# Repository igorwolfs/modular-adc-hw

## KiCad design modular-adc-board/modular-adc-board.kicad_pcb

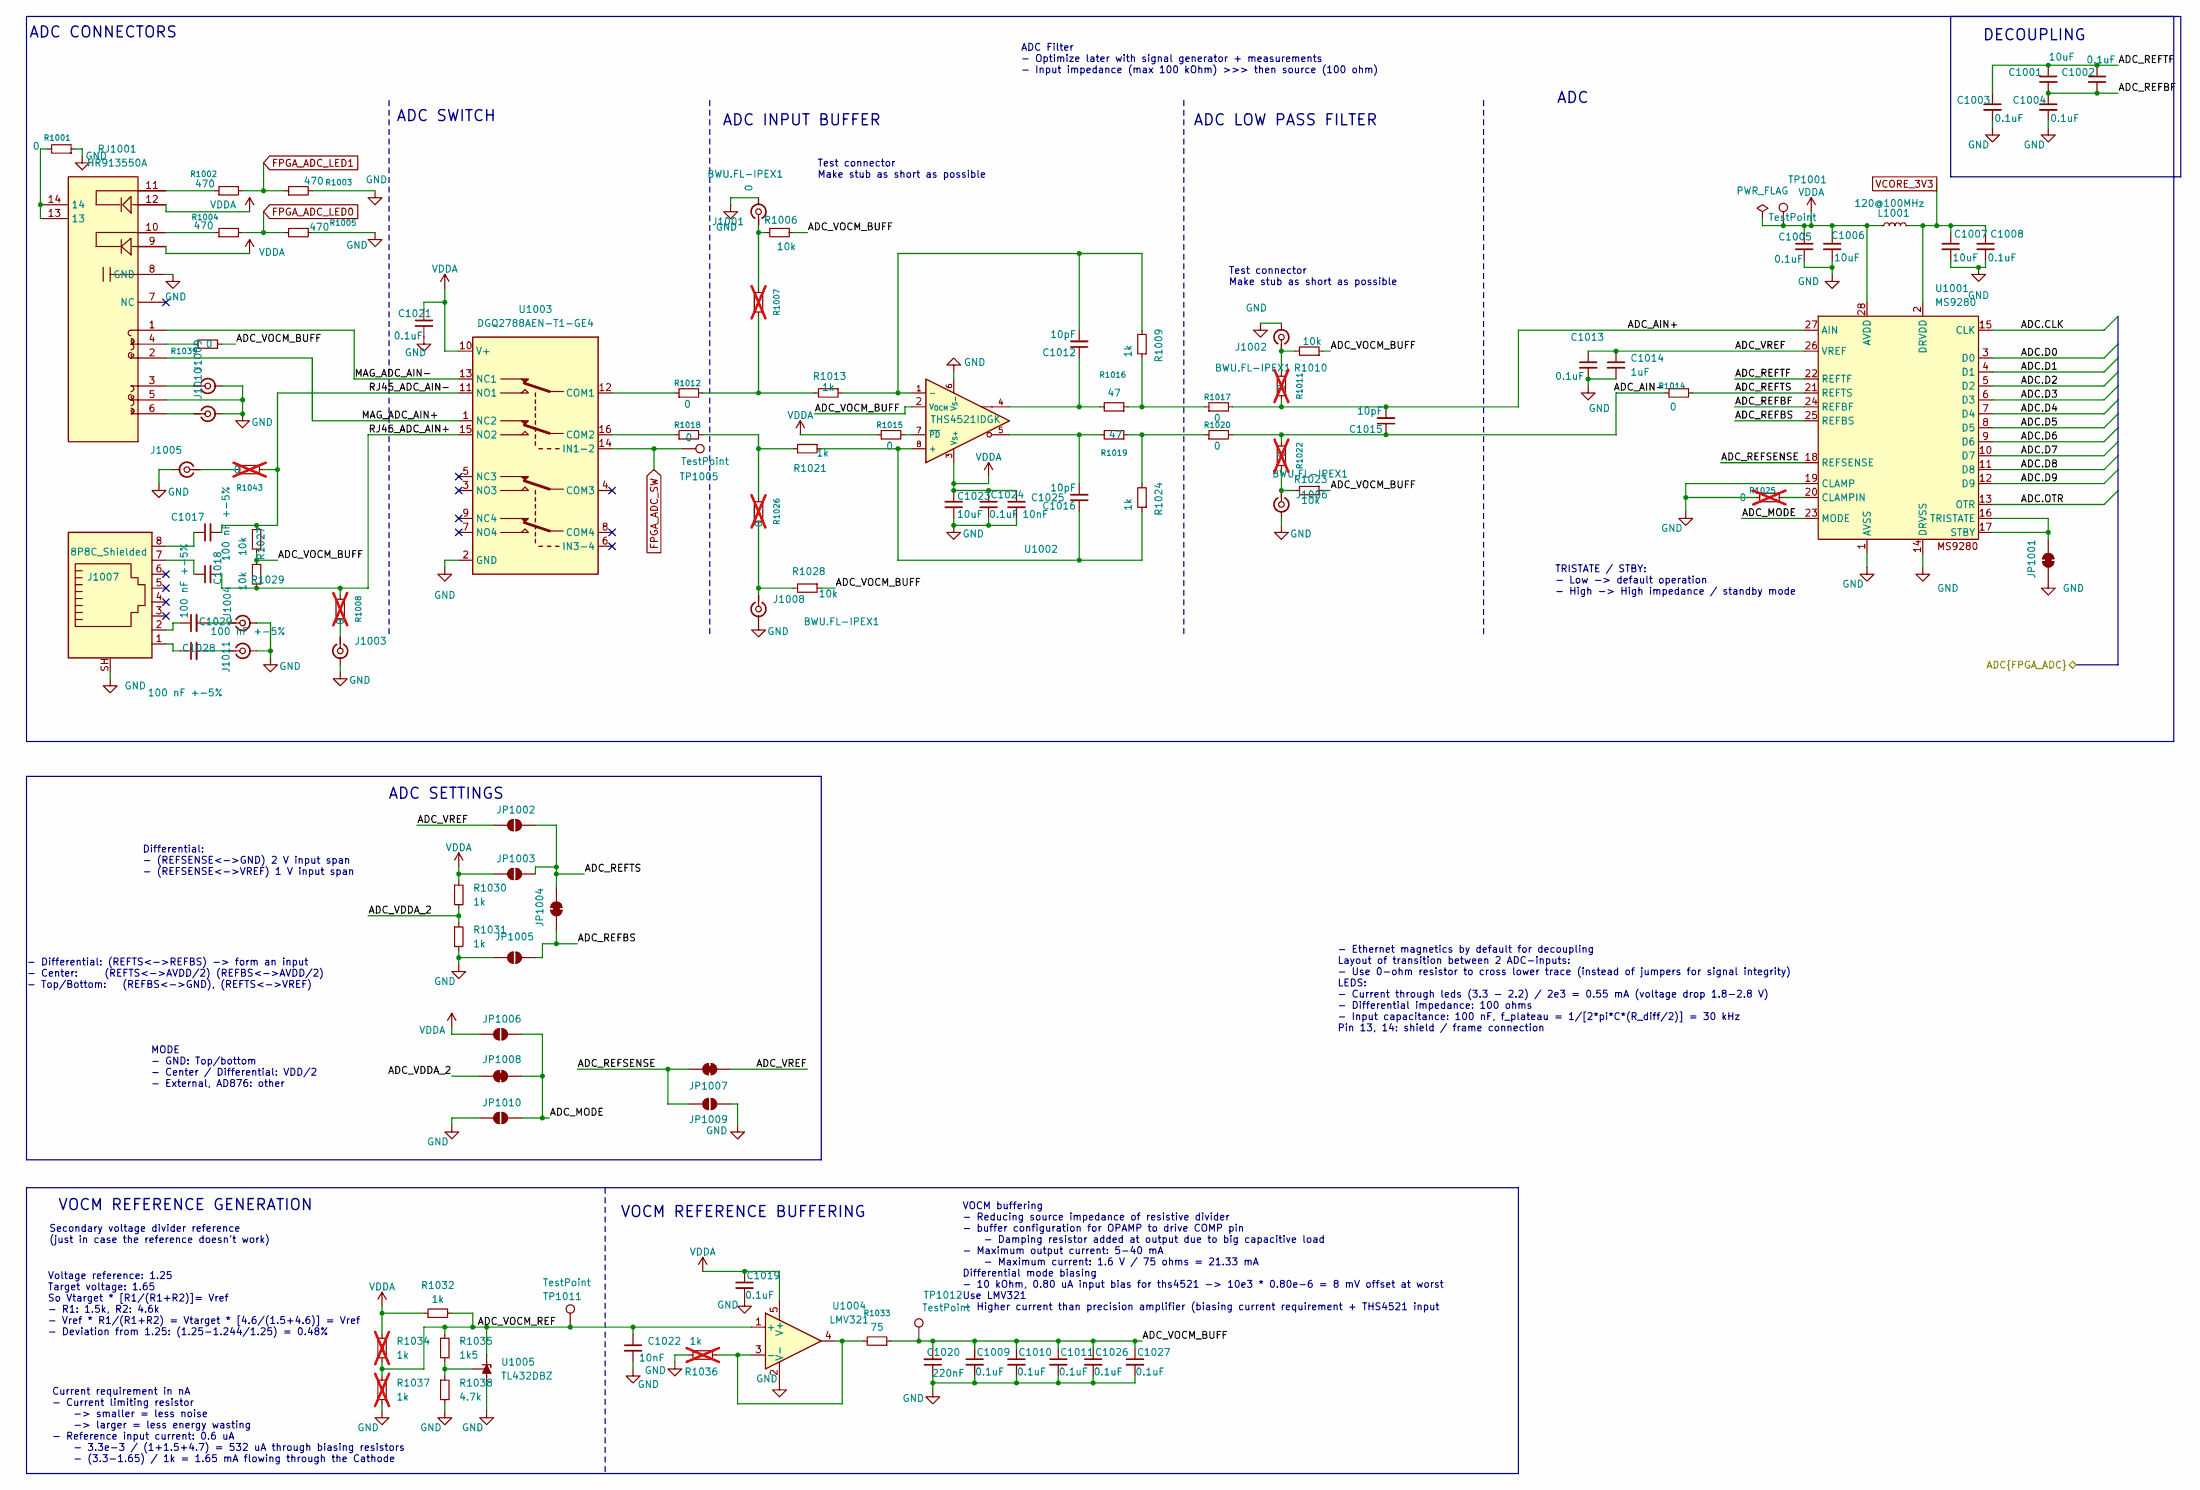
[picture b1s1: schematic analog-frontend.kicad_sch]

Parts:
C1001, C1006, C1007, C1023: 10uF; C_0603_1608Metric; Manufacturing Part Numb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 CL10A106KP8NNNC; LCSC Part Number C19702
C1002, C1003, C1004, C1005, C1008, C1009, C1010, C1011, C1013, C1019, C1021, C1024, C1026, C1027: 0.1uF; C_0201_0603Metric; Manufacturing Part Numb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 CGA0201X7R104K160ET; LCSC Part Number C22435929
C1012, C1015, C1016: 10pF; C_0603_1608Metric_Pad1.08x0.95mm_HandSolder; Manufacturing Part Numb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 CL10C100JB8NNNC; LCSC Part Number C1634
C1014: 1uF; C_0805_2012Metric; Manufacturing Part Numb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 CL21B105KBFNNNE; LCSC Part Number C28323
C1017, C1018, C1028, C1029: 100 nF +-5%; C_0603_1608Metric_Pad1.08x0.95mm_HandSolder; Manufacturing Part Numb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 0603B104J500NT; LCSC Part Number C88136
C1020: 220nF; C_0402_1005Metric; Manufacturing Part Numb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 CL05B224KO5NNNC; LCSC Part Number C16772
C1022, C1025: 10nF; C_0201_0603Metric; Manufacturing Part Numb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 0201B103K250NT; LCSC Part Number C285010
J1001, J1002, J1003, J1004, J1005, J1006, J1008, J1009, J1010, J1011: BWU.FL-IPEX1; Manufacturing Part Numb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 BWU.FL-IPEX1; LCSC Part Number C5137195
J1007: 8P8C_Shielded; RJ45_RCH_RC01937; Manufacturing Part Numb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 RC01937; LCSC Part Number C708652
JP1001, JP1004, JP1007, JP1008: SolderJumper_2_Bridged; SolderJumper-2_P1.3mm_Bridged_Pad1.0x1.5mm
JP1002, JP1003, JP1005, JP1006, JP1009, JP1010: SolderJumper_2_Open; SolderJumper-2_P1.3mm_Open_Pad1.0x1.5mm
L1001: 120@100MHz; L_0603_1608Metric; Manufacturing Part Numb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 UPB160805T-121Y-N; LCSC Part Number C285595
R1001: 0; R_0603_1608Metric_Pad0.98x0.95mm_HandSolder; Manufacturing Part Numb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 0603WAF0000T5E; LCSC Part Number C21189
R1002, R1003, R1004, R1005: 470; R_0603_1608Metric; Manufacturing Part Numb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 0603WAF4700T5E; LCSC Part Number C23179
R1006, R1010, R1023, R1027, R1028, R1029: 10k; R_0603_1608Metric; Manufacturing Part Numb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 0603WAF1002T5E; LCSC Part Number C25804
R1007, R1008, R1011, R1022, R1025, R1026, R1043: 0; R_0603_1608Metric; Manufacturing Part Numb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 0603WAF0000T5E; LCSC Part Number C21189; not fitted
R1009, R1013, R1021, R1024, R1030, R1031, R1032: 1k; R_0603_1608Metric; Manufacturing Part Numb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 0603WAF1001T5E; LCSC Part Number C21190
R1012, R1015, R1017, R1018, R1020: 0; R_0402_1005Metric_Pad0.72x0.64mm_HandSolder; Manufacturing Part Numb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 0402WGF0000TCE; LCSC Part Number C17168
R1014, R1039: 0; R_0603_1608Metric; Manufacturing Part Numb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 0603WAF0000T5E; LCSC Part Number C21189
R1016, R1019: 47; R_0603_1608Metric; Manufacturing Part Numb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 0603WAF470JT5E; LCSC Part Number C23182
R1033: 75; R_0603_1608Metric; Manufacturing Part Numb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 0603WAF750JT5E; LCSC Part Number C4275
R1034, R1036, R1037: 1k; R_0603_1608Metric; Manufacturing Part Numb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 C21190; LCSC Part Number 0603WAF1001T5E; not fitted
R1035: 1k5; R_0603_1608Metric; Manufacturing Part Numb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 0603WAF1501T5E; LCSC Part Number C22843
R1038: 4.7k; R_0603_1608Metric; Manufacturing Part Numb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 0603WAF4701T5E; LCSC Part Number C23162
RJ1001: HR913550A; RJ45-TH_HR913550A; Manufacturing Part Numb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 HR913550A; LCSC Part Number C163507
TP1001, TP1011, TP1012: TestPoint; TestPoint_Loop_D1.80mm_Drill1.0mm_Beaded
TP1005: TestPoint; TestPoint_THTPad_1.5x1.5mm_Drill0.7mm
U1001: MS9280; SSOP-28_5.3x10.2mm_P0.65mm; Manufacturing Part Numb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 MS9280; LCSC Part Number C1509021
U1002: THS4521IDGK; VSSOP-8_3x3mm_P0.65mm; Manufacturing Part Numb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 THS4521IDGKR; LCSC Part Number C170157
U1003: DGQ2788AEN-T1-GE4; QFN40P260X180X60-16N_Fv1.2; Manufacturing Part Numb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 DGQ2788AEN-T1-GE4; LCSC Part Number C2673179
U1004: LMV321; SOT-23-5; Manufacturing Part Numb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 LMV321IDBVR; LCSC Part Number C7972
U1005: TL432DBZ; SOT-23; Manufacturing Part Numb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 TL432; LCSC Part Number C5184435

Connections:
/analog-frontend/ADC.CLK: U1001.15 (CLK)
/analog-frontend/ADC.D0: U1001.3 (D0)
/analog-frontend/ADC.D1: U1001.4 (D1)
/analog-frontend/ADC.D2: U1001.5 (D2)
/analog-frontend/ADC.D3: U1001.6 (D3)
/analog-frontend/ADC.D4: U1001.7 (D4)
/analog-frontend/ADC.D5: U1001.8 (D5)
/analog-frontend/ADC.D6: U1001.9 (D6)
/analog-frontend/ADC.D7: U1001.10 (D7)
/analog-frontend/ADC.D8: U1001.11 (D8)
/analog-frontend/ADC.D9: U1001.12 (D9)
/analog-frontend/ADC.OTR: U1001.13 (OTR)
/analog-frontend/ADC_AIN+: C1015.2, R1011.1, R1017.2, U1001.27 (AIN)
/analog-frontend/ADC_AIN-: C1015.1, R1014.1, R1020.2, R1022.1
/analog-frontend/ADC_MODE: JP1006.2 (B), JP1008.2 (B), JP1010.2 (B), U1001.23 (MODE)
/analog-frontend/ADC_REFBF: C1001.2, C1002.2, C1004.1, U1001.24 (REFBF)
/analog-frontend/ADC_REFBS: JP1004.1 (A), JP1005.2 (B), U1001.25 (REFBS)
/analog-frontend/ADC_REFSENSE: JP1007.2 (B), JP1009.2 (B), U1001.18 (REFSENSE)
/analog-frontend/ADC_REFTF: C1001.1, C1002.1, C1003.1, U1001.22 (REFTF)
/analog-frontend/ADC_REFTS: JP1002.2 (B), JP1003.2 (B), JP1004.2 (B), R1014.2, U1001.21 (REFTS)
/analog-frontend/ADC_VDDA_2: JP1008.1 (A), R1030.2, R1031.1
/analog-frontend/ADC_VOCM_BUFF: C1009.1, C1010.1, C1011.1, C1020.2, C1026.1, C1027.1, R1006.1, R1010.1, R1023.1, R1027.1, R1028.1, R1029.2, R1033.1, R1039.1, TP1012.1, U1002.2 (V_{OCM})
/analog-frontend/ADC_VOCM_REF: C1022.1, R1032.2, R1034.2, R1035.1, R1037.1, TP1011.1, U1004.1 (+), U1005.2 (K)
/analog-frontend/ADC_VREF: C1013.1, C1014.1, JP1002.1 (A), JP1007.1 (A), U1001.26 (VREF)
/analog-frontend/MAG_ADC_AIN+: RJ1001.2, U1003.1 (NC2)
/analog-frontend/MAG_ADC_AIN-: RJ1001.1, U1003.13 (NC1)
/analog-frontend/RJ45_ADC_AIN+: C1018.2, R1008.1, R1029.1, U1003.15 (NO2)
/analog-frontend/RJ45_ADC_AIN-: C1017.2, R1027.2, R1043.1, U1003.11 (NO1)
FPGA_ADC_LED0: R1004.2, R1005.2
FPGA_ADC_LED1: R1002.2, R1003.1
FPGA_ADC_SW: TP1005.1, U1003.14 (IN1-2)
GND: C1003.2, C1004.2, C1005.2, C1006.2, C1007.2, C1008.2, C1009.2, C1010.2, C1011.2, C1013.2, C1014.2, C1019.2, C1020.1, C1021.2, C1022.2, C1023.2, C1024.2, C1025.2, C1026.2, C1027.2, J1001.2 (Ext), J1002.2 (Ext), J1003.2 (Ext), J1004.2 (Ext), J1005.2 (Ext), J1006.2 (Ext), J1007.SH, J1008.2 (Ext), J1009.2 (Ext), J1010.2 (Ext), J1011.2 (Ext), JP1001.1 (A), JP1005.1 (A), JP1009.1 (A), JP1010.1 (A), R1001.1, R1003.2, R1005.1, R1025.1, R1031.2, R1036.1, R1037.2, R1038.2, RJ1001.5, RJ1001.8 (GND), U1001.1 (AVSS), U1001.14 (DRVSS), U1001.19 (CLAMP), U1002.6 (V_{S-}), U1003.2 (GND), U1004.2 (V-), U1005.3 (A)
unnamed: C1012.1, R1016.2, U1002.4
unnamed: C1016.2, R1019.2, U1002.5
unnamed: C1017.1, J1007.8
unnamed: C1018.1, J1007.7
unnamed: C1028.1, J1007.1
unnamed: C1029.1, J1007.2
unnamed: J1001.1 (In), R1006.2, R1007.1
unnamed: J1002.1 (In), R1010.2, R1011.2
unnamed: J1003.1 (In), R1008.2
unnamed: C1029.2, J1004.1 (In)
unnamed: J1005.1 (In), R1043.2
unnamed: J1006.1 (In), R1022.2, R1023.2
unnamed: J1008.1 (In), R1026.2, R1028.2
unnamed: J1009.1 (In), RJ1001.3
unnamed: J1010.1 (In), RJ1001.6
unnamed: C1028.2, J1011.1 (In)
unnamed: JP1001.2 (B), U1001.16 (TRISTATE), U1001.17 (STBY)
unnamed: R1001.2, RJ1001.13, RJ1001.14
unnamed: R1002.1, RJ1001.11
unnamed: R1004.1, RJ1001.10
unnamed: R1007.2, R1012.2, R1013.2
unnamed: R1009.1, R1016.1, R1017.1
unnamed: R1018.2, R1021.2, R1026.1
unnamed: R1019.1, R1020.1, R1024.2
unnamed: R1039.2, RJ1001.4
unnamed: R1025.2, U1001.20 (CLAMPIN)
unnamed: C1016.1, R1021.1, R1024.1, U1002.8 (+)
unnamed: C1012.2, R1009.2, R1013.1, U1002.1 (-)
unnamed: R1015.2, U1002.7 (~PD)
unnamed: R1012.1, U1003.12 (COM1)
unnamed: R1018.1, U1003.16 (COM2)
unnamed: R1033.2, R1036.2, U1004.3 (-), U1004.4
unnamed: R1035.2, R1038.1, U1005.1 (REF)
VCORE_3V3: C1007.1, C1008.1, L1001.1, U1001.2 (DRVDD)
VDDA: C1005.1, C1006.1, C1019.1, C1021.1, C1023.1, C1024.1, C1025.1, JP1003.1 (A), JP1006.1 (A), L1001.2, R1015.1, R1030.1, R1032.1, R1034.1, RJ1001.9, RJ1001.12, TP1001.1, U1001.28 (AVDD), U1002.3 (V_{S+}), U1003.10 (V+), U1004.5 (V+)

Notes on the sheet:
ADC CONNECTORS
ADC SETTINGS
VOCM REFERENCE BUFFERING
Test connector Make stub as short as possible
ADC INPUT BUFFER
VOCM REFERENCE GENERATION
ADC Filter - Optimize later with signal generator + measurements - Input impedance (max 100 kOhm) >>> then source (100 ohm)
Secondary voltage divider reference (just in case the reference doesn't work)
TRISTATE / STBY: - Low -> default operation - High -> High impedance / standby mode
DECOUPLING
Current requirement in nA - Current limiting resistor -> smaller = less noise -> larger = less energy wasting - Reference input current: 0.6 uA - 3.3e-3 / (1+1.5+4.7) = 532 uA through biasing resistors - (3.3-1.65) / 1k = 1.65 mA flowing through the Cathode
ADC SWITCH
VOCM buffering - Reducing source impedance of resistive divider - buffer configuration for OPAMP to drive COMP pin - Damping resistor added at output due to big capacitive load - Maximum output current: 5-40 mA - Maximum current: 1.6 V / 75 ohms = 21.33 mA Differential mode biasing - 10 kOhm, 0.80 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
Differential: - (REFSENSE<->GND) 2 V input span - (REFSENSE<->VREF) 1 V input span
MODE - GND: Top/bottom - Center / Differential: VDD/2 - External, AD876: other
- Differential: (REFTS<->REFBS) -> form an input - Center: (REFTS<->AVDD/2) (REFBS<->AVDD/2) - Top/Bottom: (REFBS<->GND), (REFTS<->VREF)
Voltage reference: 1.25 Target voltage: 1.65 So Vtarget * [R1/(R1+R2)]= Vref - R1: 1.5k, R2: 4.6k - Vref * R1/(R1+R2) = Vtarget * [4.6/(1.5+4.6)] = Vref - Deviation from 1.25: (1.25-1.244/1.25) = 0.48%
- Ethernet magnetics by default for decoupling Layout of transition between 2 ADC-inputs: - Use 0-ohm resistor to cross lower trace (instead of jumpers for signal integrity) LEDS: - Current through leds (3.3 - 2.2) / 2e3 = 0.55 mA (voltage drop 1.8-2.8 V) - Differential impedance: 100 ohms - Input 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
ADC
ADC LOW PASS FILTER

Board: 2 copper layers, 101 parts (0 on the bottom side), 55 nets, no tracks yet.

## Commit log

2025-10-25 minor board changes, notes on double-adc usage, added simulations
